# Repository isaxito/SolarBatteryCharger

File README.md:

STM32F103T8 based Battery charger using a 10W solar panel. This is part of my Engineering degree final project.

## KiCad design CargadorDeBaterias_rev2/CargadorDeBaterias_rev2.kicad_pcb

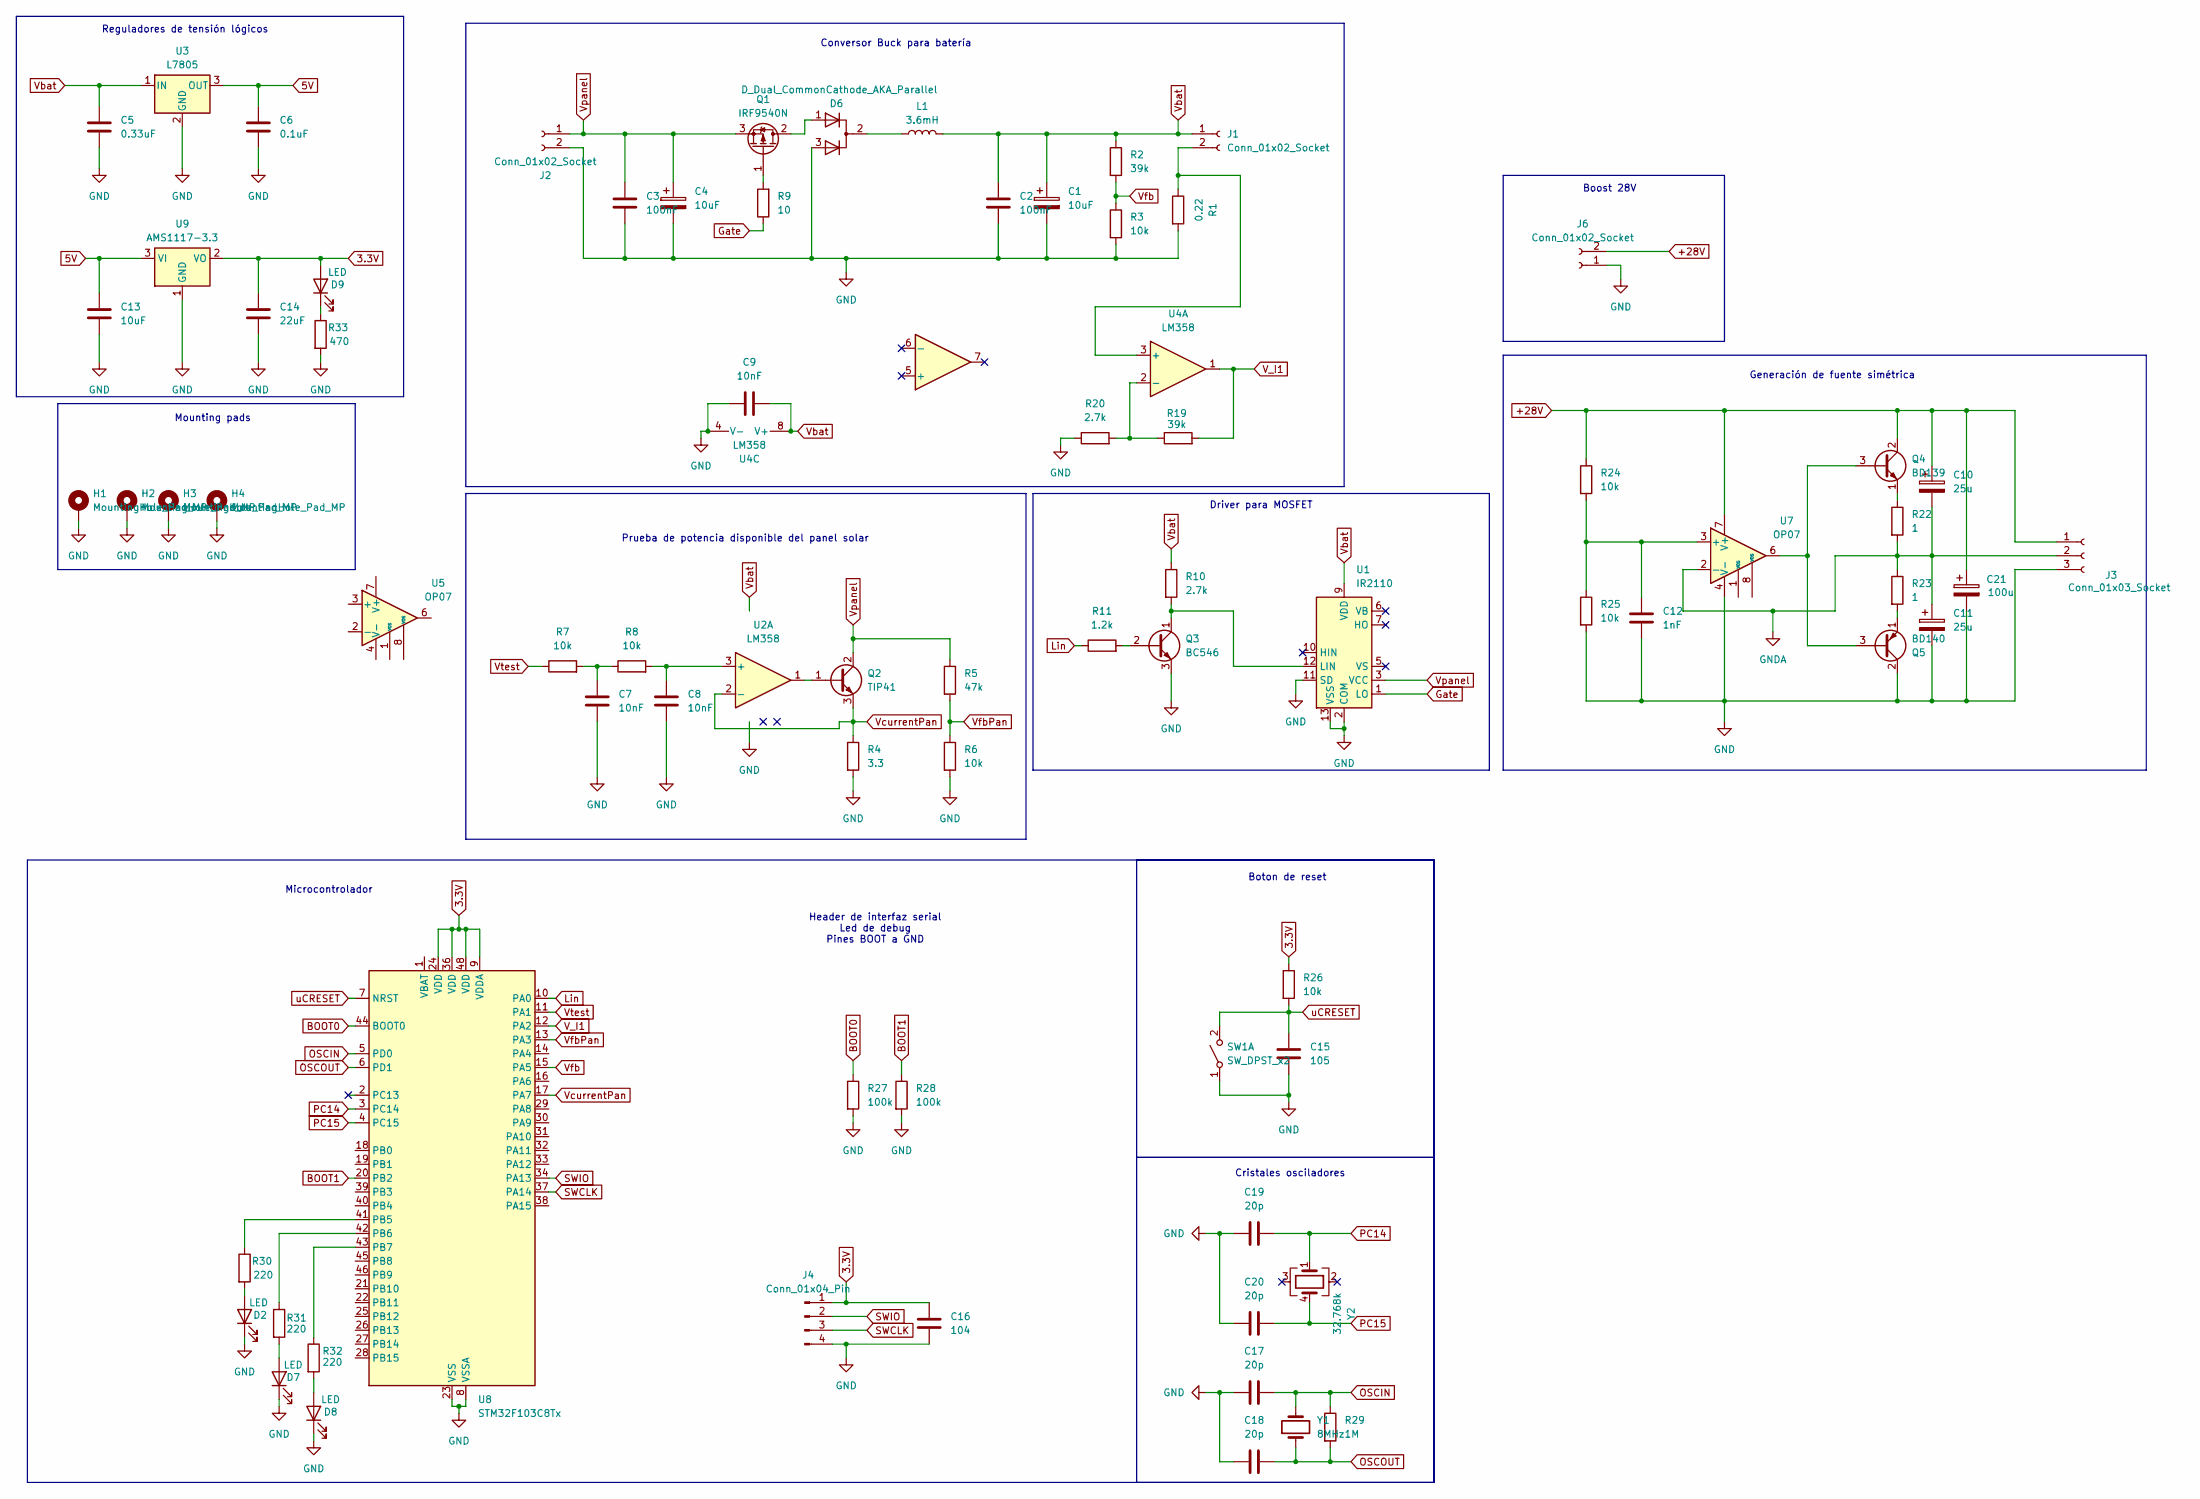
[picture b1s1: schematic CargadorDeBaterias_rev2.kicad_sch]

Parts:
C1, C4: 10uF; CP_Radial_D5.0mm_P2.50mm
C2, C3: 100nF; C_Disc_D5.0mm_W2.5mm_P5.00mm
C5: 0.33uF; C_Disc_D5.0mm_W2.5mm_P5.00mm
C6: 0.1uF; C_Disc_D5.0mm_W2.5mm_P5.00mm
C7, C8, C9: 10nF; C_Disc_D5.0mm_W2.5mm_P5.00mm
C10, C11: 25u; CP_Radial_D5.0mm_P2.50mm
C12: 1nF; C_Disc_D5.0mm_W2.5mm_P5.00mm
C13: 10uF; C_Disc_D5.0mm_W2.5mm_P5.00mm
C14: 22uF; C_Disc_D5.0mm_W2.5mm_P5.00mm
C15: 105; C_0603_1608Metric_Pad1.08x0.95mm_HandSolder
C16: 104; C_0603_1608Metric_Pad1.08x0.95mm_HandSolder
C17, C18, C19, C20: 20p; C_0603_1608Metric_Pad1.08x0.95mm_HandSolder
C21: 100u; CP_Radial_D6.3mm_P2.50mm
D2, D7, D8, D9: LED; LED_D5.0mm_FlatTop
D6: D_Dual_CommonCathode_AKA_Parallel; TO-220-3_Vertical
H1, H2, H3, H4: MountingHole_Pad_MP; MountingHole_3mm_Pad
J1, J2, J6: Conn_01x02_Socket; TerminalBlock_bornier-2_P5.08mm
J3: Conn_01x03_Socket; TerminalBlock_bornier-3_P5.08mm
J4: Conn_01x04_Pin; PinHeader_1x04_P2.54mm_Horizontal
L1: 3.6mH; L_Radial_D7.5mm_P3.50mm_Fastron_07P
Q1: IRF9540N; TO-220-3_Vertical
Q2: TIP41; TO-220-3_Vertical
Q3: BC546; TO-92_Inline_Wide
Q4: BD139; TO-126-3_Vertical
Q5: BD140; TO-126-3_Vertical
R1: 0.22; R_Axial_DIN0207_L6.3mm_D2.5mm_P10.16mm_Horizontal
R2, R19: 39k; R_Axial_DIN0207_L6.3mm_D2.5mm_P10.16mm_Horizontal
R3, R6, R7, R8, R24, R25, R26: 10k; R_Axial_DIN0207_L6.3mm_D2.5mm_P10.16mm_Horizontal
R4: 3.3; R_Axial_DIN0207_L6.3mm_D2.5mm_P10.16mm_Horizontal
R5: 47k; R_Axial_DIN0207_L6.3mm_D2.5mm_P10.16mm_Horizontal
R9: 10; R_Axial_DIN0207_L6.3mm_D2.5mm_P10.16mm_Horizontal
R10, R20: 2.7k; R_Axial_DIN0207_L6.3mm_D2.5mm_P10.16mm_Horizontal
R11: 1.2k; R_Axial_DIN0207_L6.3mm_D2.5mm_P10.16mm_Horizontal
R22, R23: 1; R_Axial_DIN0207_L6.3mm_D2.5mm_P10.16mm_Horizontal
R27, R28: 100k; R_Axial_DIN0207_L6.3mm_D2.5mm_P10.16mm_Horizontal
R29: 1M; R_Axial_DIN0207_L6.3mm_D2.5mm_P10.16mm_Horizontal
R30, R31, R32: 220; R_Axial_DIN0207_L6.3mm_D2.5mm_P10.16mm_Horizontal
R33: 470; R_Axial_DIN0207_L6.3mm_D2.5mm_P10.16mm_Horizontal
SW1: SW_DPST_x2; SW_SPST_EVQPE1
U1: IR2110; DIP-14_W7.62mm
U2, U4: LM358; DIP-8_W7.62mm
U3: L7805; TO-220-3_Vertical
U5, U7: OP07; DIP-8_W7.62mm
U8: STM32F103C8Tx; LQFP-48_7x7mm_P0.5mm
U9: AMS1117-3.3; SOT-223-3_TabPin2
Y1: 8MHz; Resonator-2Pin_W8.0mm_H3.5mm
Y2: 32.768k; OSCL550P800X320X254-4N

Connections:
3.3V: C14.1, C16.1, D9.2 (A), J4.1, R26.1, U8.9 (VDDA), U8.24 (VDD), U8.36 (VDD), U8.48 (VDD), U9.2 (VO)
5V: C6.1, C13.1, U3.3 (OUT), U9.3 (VI)
+28V: C10.1, C21.1, J3.1, J6.2, Q4.2 (C), R24.1, U7.7 (V+)
BOOT0: R27.1, U8.44 (BOOT0)
BOOT1: R28.1, U8.20 (PB2)
GND: C1.2, C2.2, C3.2, C4.2, C5.2, C6.2, C7.2, C8.2, C9.1, C11.2, C12.2, C13.2, C14.2, C15.2, C16.2, C17.1, C18.1, C19.1, C20.1, C21.2, D2.1 (K), D6.3 (A), D7.1 (K), D8.1 (K), H1.MP, H2.MP, H3.MP, H4.MP, J2.2, J3.3, J4.4, J6.1, Q3.3 (E), Q5.2 (C), R1.2, R3.2, R4.2, R6.2, R20.1, R25.2, R27.2, R28.2, R33.2, SW1.1 (A), U1.2 (COM), U1.11 (SD), U1.13 (VSS), U3.2 (GND), U4.4 (V-), U5.4 (V-), U7.4 (V-), U8.8 (VSSA), U8.23 (VSS), U8.35 (VSS), U8.47 (VSS), U9.1 (GND)
GNDA: C10.2, C11.1, J3.2, R22.2, R23.1, U7.2 (-)
Gate: R9.1, U1.1 (LO)
Lin: R11.1, U8.10 (PA0)
unnamed: C7.1, R7.2, R8.1
unnamed: D2.2 (A), R30.2
unnamed: D6.2 (K), L1.1
unnamed: D7.2 (A), R31.2
unnamed: D8.2 (A), R32.2
unnamed: D9.1 (K), R33.1
unnamed: J1.2, R1.1, U4.3 (+)
unnamed: D6.1 (A), Q1.2 (D)
unnamed: Q1.1 (G), R9.2
unnamed: Q2.1 (B), U2.1, U5.6
unnamed: Q3.2 (B), R11.2
unnamed: Q3.1 (C), R10.2, U1.12 (LIN)
unnamed: Q4.3 (B), Q5.3 (B), U7.6
unnamed: Q4.1 (E), R22.1
unnamed: Q5.1 (E), R23.2
unnamed: R19.1, R20.2, U4.2 (-)
unnamed: C12.1, R24.2, R25.1, U7.3 (+)
unnamed: R30.1, U8.41 (PB5)
unnamed: R31.1, U8.42 (PB6)
unnamed: R32.1, U8.43 (PB7)
OSCIN: C17.2, R29.1, U8.5 (PD0), Y1.2
OSCOUT: C18.2, R29.2, U8.6 (PD1), Y1.1
PC14: C19.2, U8.3 (PC14), Y2.1
PC15: C20.2, U8.4 (PC15), Y2.4
SWCLK: J4.3, U8.37 (PA14)
SWIO: J4.2, U8.34 (PA13)
V_I1: R19.2, U4.1, U8.12 (PA2)
Vbat: C1.1, C2.1, C5.1, C9.2, J1.1, L1.2, R2.1, R10.1, U1.9 (VDD), U3.1 (IN), U4.8 (V+), U5.7 (V+)
VcurrentPan: Q2.3 (E), R4.1, U2.2 (-), U5.2 (-), U8.17 (PA7)
Vfb: R2.2, R3.1, U8.15 (PA5)
VfbPan: R5.2, R6.1, U8.13 (PA3)
Vpanel: C3.1, C4.1, J2.1, Q1.3 (S), Q2.2 (C), R5.1, U1.3 (VCC)
Vtest: R7.1, U8.11 (PA1)
uCRESET: C15.1, R26.2, SW1.2 (B), U8.7 (NRST)

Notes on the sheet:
Microcontrolador
Header de interfaz serial Led de debug Pines BOOT a GND
Boton de reset
Cristales osciladores
Conversor Buck para batería
Mounting pads
Driver para MOSFET
Boost 28V
Generación de fuente simétrica
Prueba de potencia disponible del panel solar
Reguladores de tensión lógicos

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
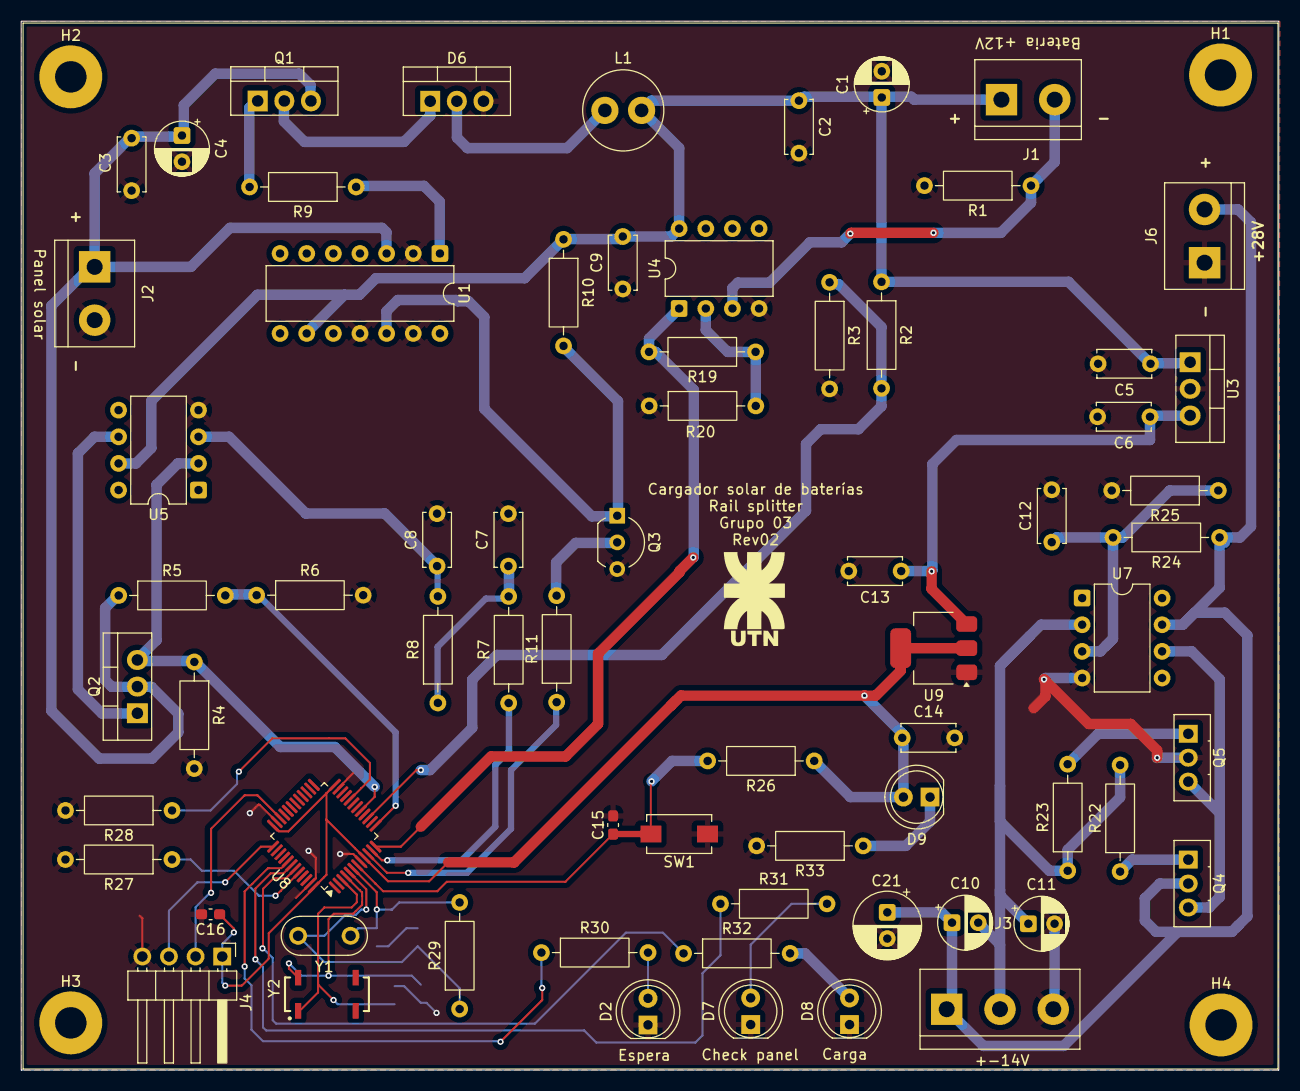
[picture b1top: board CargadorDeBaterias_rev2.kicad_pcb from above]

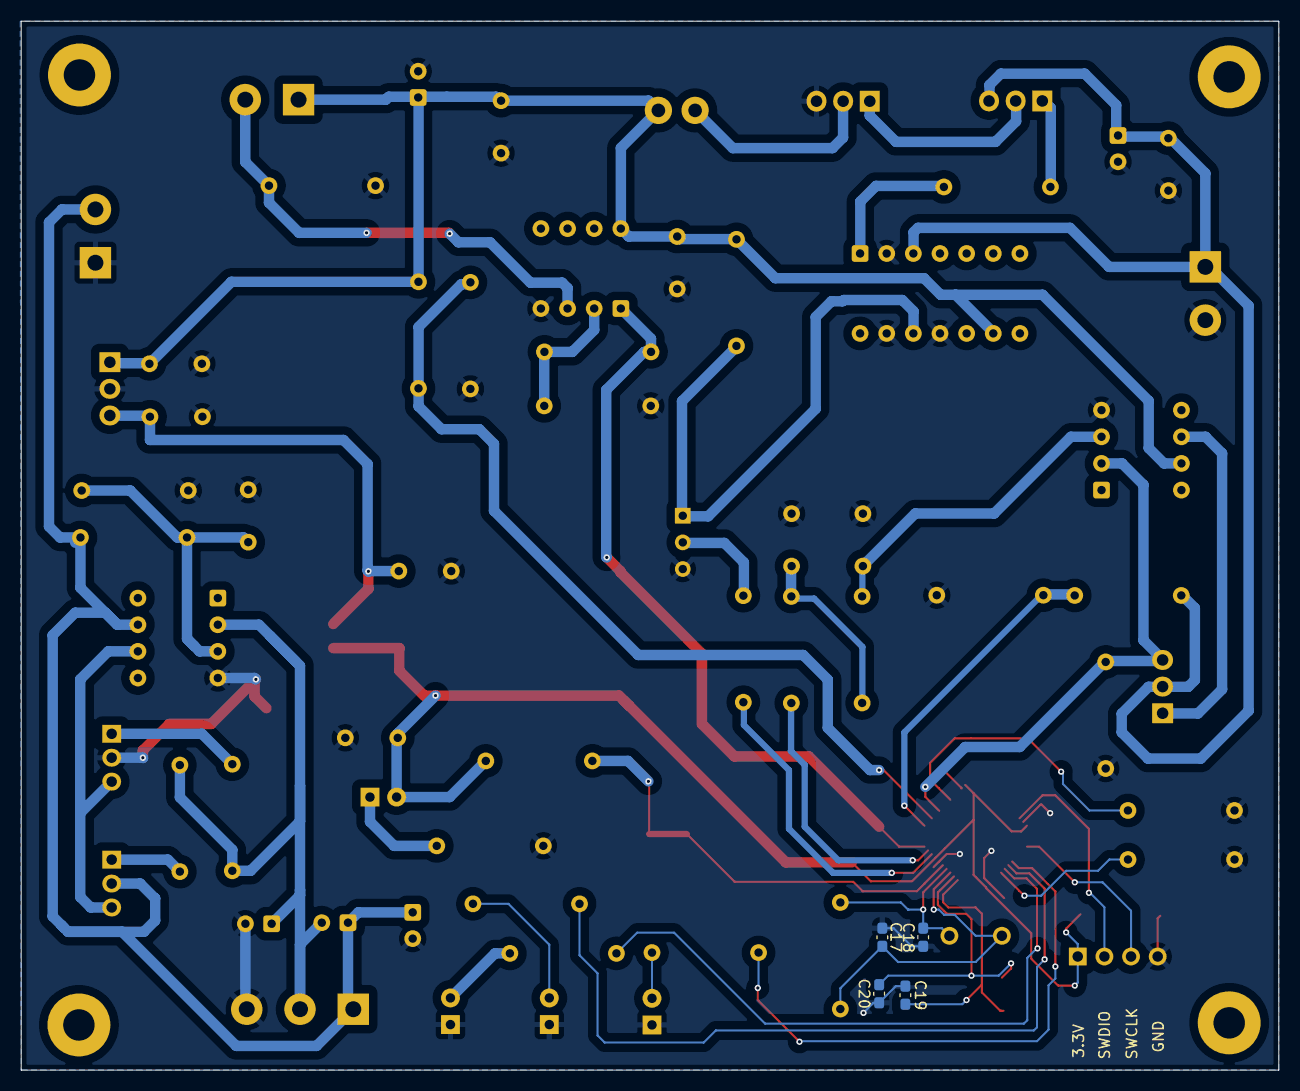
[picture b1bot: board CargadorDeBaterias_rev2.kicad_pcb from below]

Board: 2 copper layers, 119.9 x 100.0 mm, 76 parts (4 on the bottom side), 44 nets.

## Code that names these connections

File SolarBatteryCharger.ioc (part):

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Mcu.Name=STM32F103C(8-B)Tx
Mcu.Package=LQFP48
Mcu.UserName=STM32F103C8Tx
PA0-WKUP.Signal=S_TIM2_CH1_ETR
PA1.Signal=S_TIM2_CH2
PA13.Mode=Serial_Wire
PA13.Signal=SYS_JTMS-SWDIO
PA14.Mode=Serial_Wire
PA14.Signal=SYS_JTCK-SWCLK
PA2.Signal=ADCx_IN2
PA3.Signal=ADCx_IN3
PA5.Signal=ADCx_IN5
PA7.Signal=ADCx_IN7
PB5.Signal=GPIO_Output
PB6.Signal=GPIO_Output
PB7.Signal=GPIO_Output
PC13-TAMPER-RTC.GPIOParameters=GPIO_PuPd
PC13-TAMPER-RTC.GPIO_PuPd=GPIO_NOPULL
PC13-TAMPER-RTC.Signal=GPIO_Output
PD0-OSC_IN.Mode=HSE-External-Oscillator
PD0-OSC_IN.Signal=RCC_OSC_IN
PD1-OSC_OUT.Mode=HSE-External-Oscillator
PD1-OSC_OUT.Signal=RCC_OSC_OUT
RCC.SYSCLKFreq_VALUE=72000000
RCC.SYSCLKSource=RCC_SYSCLKSOURCE_PLLCLK
board=custom

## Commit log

2025-07-24 First commit of the project
2025-07-30 Advances in main code. Addition of .gitignore
2025-08-14 Last advances. At this point, the charger is working with major modifications in the circuit.
2025-09-26 Last changes after incident
2025-11-28 Upload last changes for final circuit
2025-11-28 Upload kicad files
2025-12-12 Upload last changes. Increase charge current, correct R19. Change panel voltage limits
2026-01-29 Lower maximum battery voltage control
